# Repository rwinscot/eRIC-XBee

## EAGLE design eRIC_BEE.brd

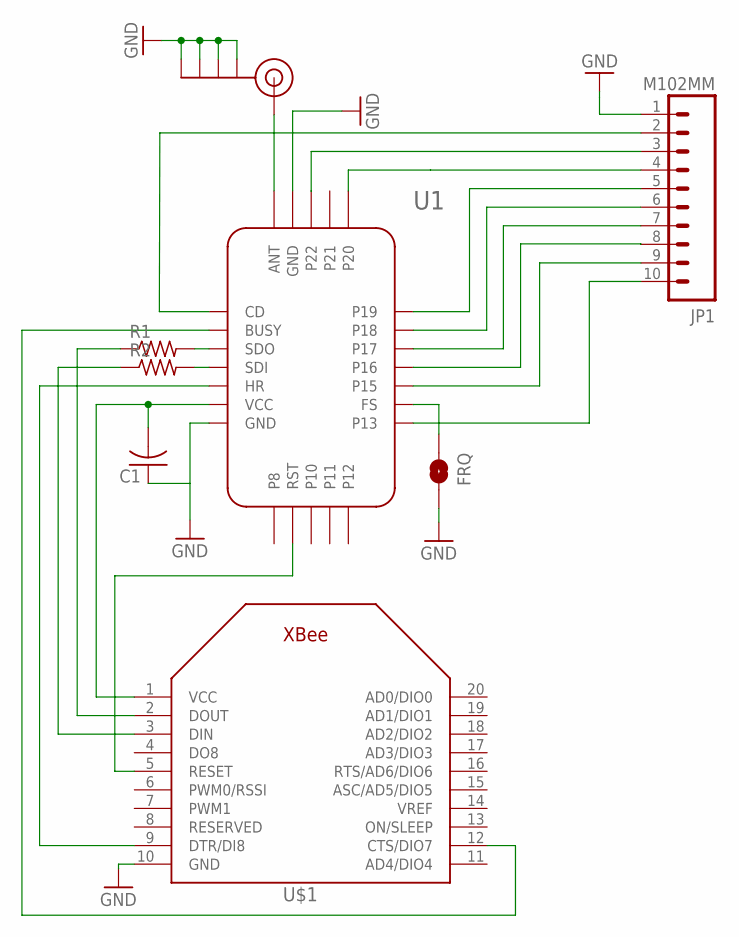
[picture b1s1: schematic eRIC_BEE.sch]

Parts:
C1: C-USC0402; C0402
FRQ: JUMPER-PAD-2-NOYES_SILK; PAD-JUMPER-2-NO_YES_SILK
J$2: SMA_EDGE; SMA-EDGE
JP1: M102MM; 1X10-2MM
R1, R2: R-US_R0402; R0402
U1: ERIC
U$1: XBEE

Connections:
GND: C1.1, FRQ.2, J$2.GND@0 (GND), J$2.GND@1 (GND), J$2.GND@2 (GND), J$2.GND@3 (GND), JP1.1, U1.AGND (GND), U1.GND, U$1.10 (GND)
unnamed: FRQ.1, U1.FS
unnamed: R1.1, U$1.2 (DOUT)
unnamed: R2.1, U$1.3 (DIN)
unnamed: J$2.SIG (SIGNAL), U1.ANT
unnamed: U1.HR, U$1.9 (DTR/DI8)
unnamed: R2.2, U1.SDI
unnamed: U1.BUSY, U$1.12 (CTS/DIO7)
unnamed: R1.2, U1.SDO
unnamed: JP1.4, U1.E20 (P20)
unnamed: JP1.2, U1.CD
unnamed: JP1.3, U1.E22 (P22)
unnamed: JP1.5, U1.E19 (P19)
unnamed: JP1.6, U1.E18 (P18)
unnamed: JP1.7, U1.E17 (P17)
unnamed: JP1.8, U1.E16 (P16)
unnamed: JP1.9, U1.E15 (P15)
unnamed: JP1.10, U1.E13 (P13)
unnamed: U1.E9 (RST), U$1.5 (RESET)
VCC: C1.2, U1.VCC, U$1.1 (VCC)

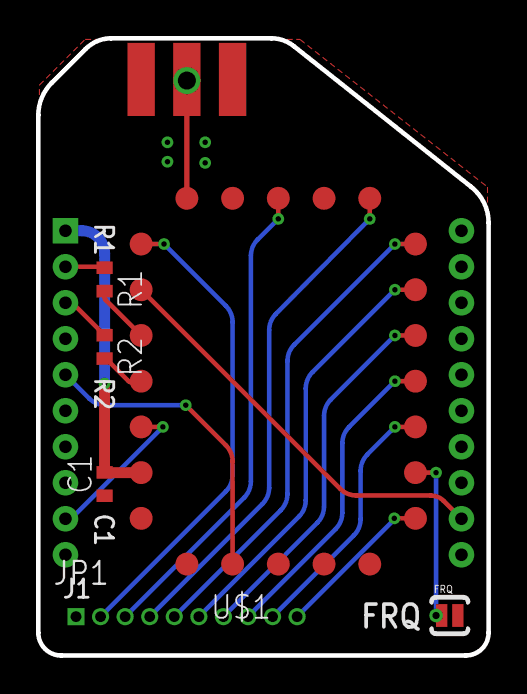
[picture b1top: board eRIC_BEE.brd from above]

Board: 2 copper layers, 25.0 x 34.3 mm, 8 parts (0 on the bottom side), 20 nets.

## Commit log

2015-04-09 board outline, widen pin spacing, move SMA connector forward
2015-04-09 BOM, component names and values
2015-04-12 added wire antenna option
2015-04-12 wire option size - reduced
2015-04-30 revision 1.8, eagle 7.2 cam, new board design to eliminate need for wonky stitching

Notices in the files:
parts and their libraries:
SparkFun-Connectors: Licensing: Creative Commons ShareAlike 4.0 International - https://creativecommons.org/licenses/by-sa/4.0
